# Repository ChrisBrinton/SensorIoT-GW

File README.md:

# SensorIoT

Consolidated repository for the SensorIoT environmental sensing system — all embedded firmware and hardware designs.

## Architecture

```
Sensor Nodes (ATmega328P + BME280 + RF95/RFM69)
        │
        │  915 MHz packet radio
        ▼
Gateway (ESP8266 + RF radio + WiFi + OLED)
        │
        │  WiFi / MQTT
        ▼
Backend Server (see SensorIoT-Broker repo)
```

## Components

### firmware/gateway/
ESP8266-based gateway that receives sensor data from nodes via RF radio and publishes to MQTT.
- RFM69 / RF95 (LoRa) radio receiver
- MQTT publisher over WiFi
- 128x32 OLED display for real-time readings
- Embedded web interface for configuration
- OTA firmware updates
- Built with PlatformIO

### firmware/node/
Battery-operated sensor nodes (ATmega328P) that measure temperature, humidity, and pressure.
- BME280 environmental sensor
- RFM69 / RF95 radio transmitter
- Low-power sleep modes for extended battery life
- Multiple firmware variants (RadioHead, RFM69, power-boost)
- Built with PlatformIO

### firmware/display/
ESP32-based standalone display module (work in progress).
- ESP32-WROVER-IE with WiFi/BLE
- LTR-329 ambient light sensor

### PCBs/
EAGLE CAD hardware designs for all boards:
- `gateway/` — Gateway board revisions (v1.13–1.16)
- `node/` — Sensor node board revisions (v1.3b–1.5)
- `display/` — Display module board
- `accessories/` — BME280 daughter boards, ISP programmers

## Sensors

| Measurement | Sensor | Units |
|-------------|--------|-------|
| Temperature | BME280 | °F |
| Humidity | BME280 | % RH |
| Pressure | BME280 | inHg |
| Battery | ADC | V |
| Signal | RSSI | dBm |

## Building

Each firmware component has its own PlatformIO project:

```bash
cd firmware/gateway
pio run                    # Build
pio run -t upload          # Flash via USB
pio run -e ota -t upload   # Flash via OTA
```

## Related Repositories

- **SensorIoT-Broker** — Backend services (MQTT broker, REST API, MongoDB)
- **SensorIoT_app** — React Native mobile app

## Consolidation History

This repo now contains code previously split across:
- `SensorIoT-GW` — Gateway firmware and PCBs (original home of this repo)
- `SensorIoT-Node` — Sensor node firmware and PCBs
- `SensorIoT-Display` — Display module hardware and firmware

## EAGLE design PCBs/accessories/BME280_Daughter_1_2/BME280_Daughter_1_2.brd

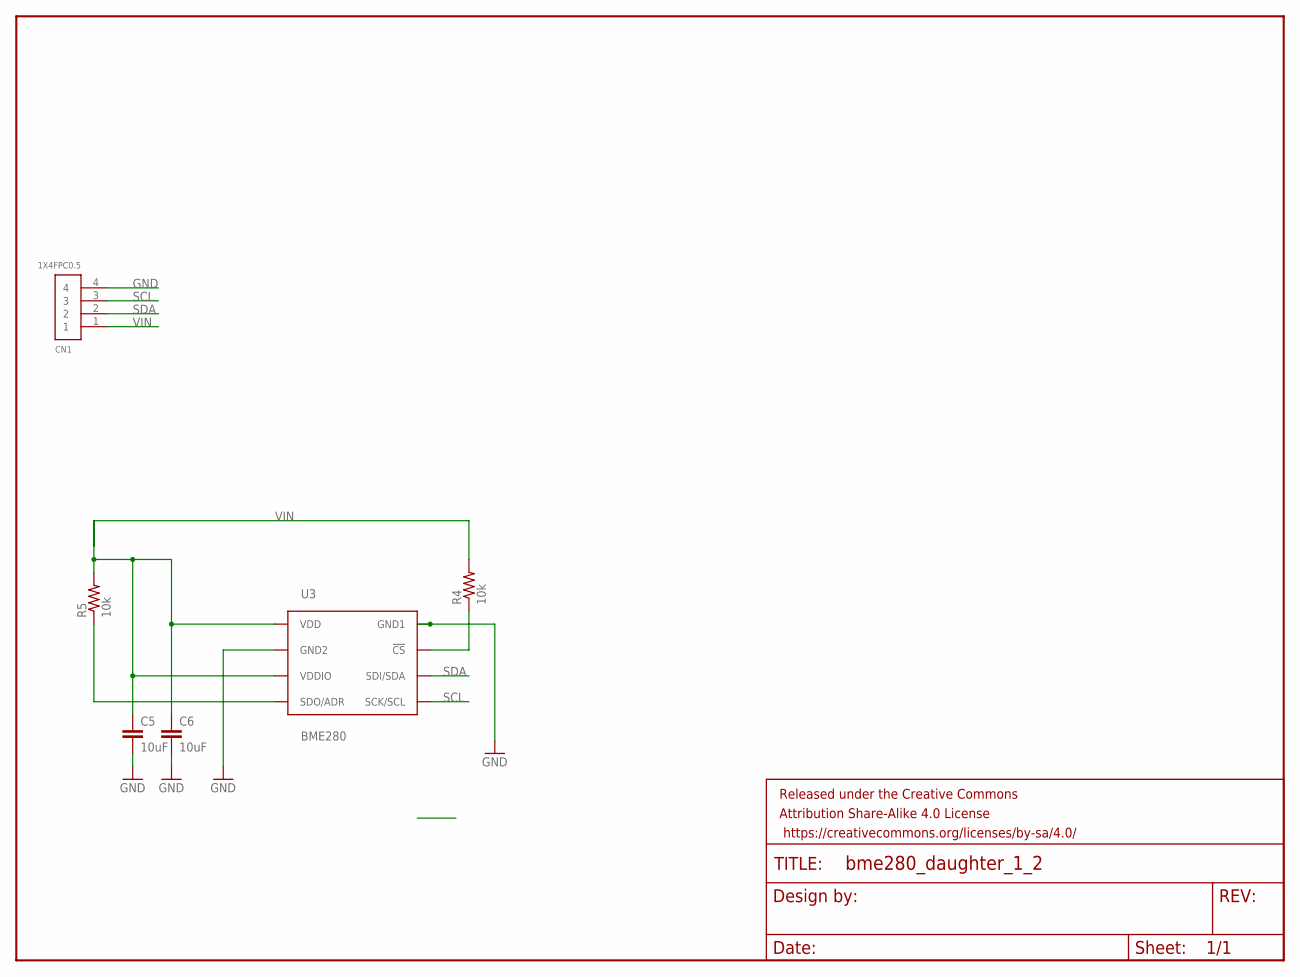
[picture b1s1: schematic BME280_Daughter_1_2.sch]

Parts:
C5, C6: 10uF; 0805
CN1: 1X4FPC0.5; FPC_0.5MM-4
FRAME1: FRAME-LETTER; CREATIVE_COMMONS
R4, R5: 10k; 0805
U3: BME280; BME280_LGA

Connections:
GND: C5.2, C6.2, CN1.4, U3.P$1 (GND1), U3.P$7 (GND2)
unnamed: R4.1, U3.P$2 (!CS)
unnamed: R5.1, U3.P$5 (SDO/ADR)
SCL: CN1.3, U3.P$4 (SCK/SCL)
SDA: CN1.2, U3.P$3 (SDI/SDA)
VIN: C5.1, C6.1, CN1.1, R4.2, R5.2, U3.P$6 (VDDIO), U3.P$8 (VDD)

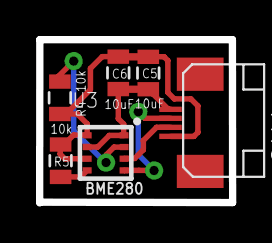
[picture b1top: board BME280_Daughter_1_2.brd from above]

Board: 2 copper layers, 10.7 x 9.1 mm, 7 parts (0 on the bottom side), 6 nets.

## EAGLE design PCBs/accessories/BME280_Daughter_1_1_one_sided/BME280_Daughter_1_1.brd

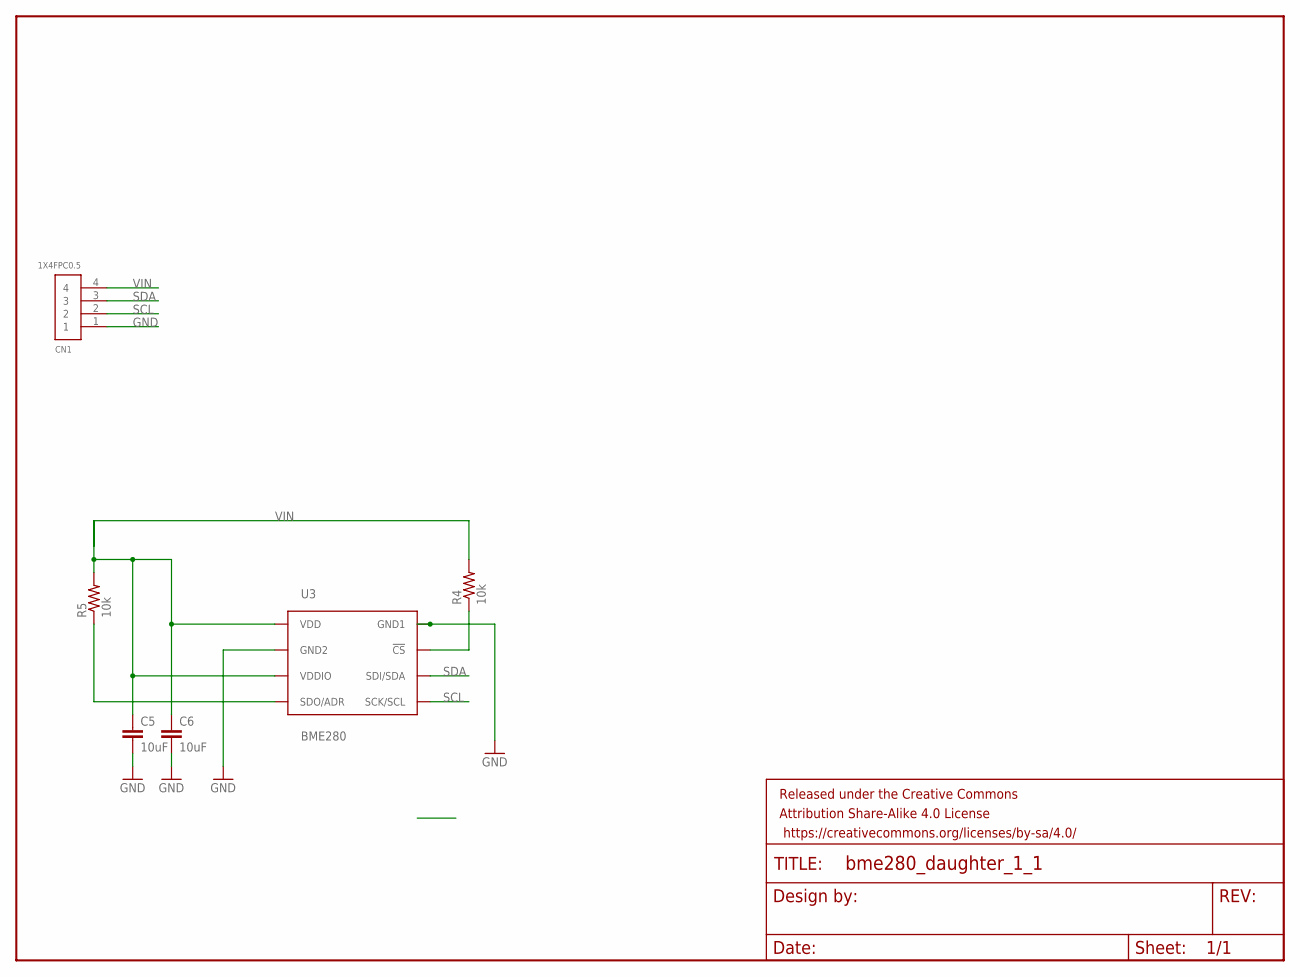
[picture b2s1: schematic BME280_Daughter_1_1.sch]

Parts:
C5, C6: 10uF; 0805
CN1: 1X4FPC0.5; FPC_0.5MM-4
FRAME1: FRAME-LETTER; CREATIVE_COMMONS
R4, R5: 10k; 0805
U3: BME280; BME280_LGA

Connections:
GND: C5.2, C6.2, CN1.1, U3.P$1 (GND1), U3.P$7 (GND2)
unnamed: R4.1, U3.P$2 (!CS)
unnamed: R5.1, U3.P$5 (SDO/ADR)
SCL: CN1.2, U3.P$4 (SCK/SCL)
SDA: CN1.3, U3.P$3 (SDI/SDA)
VIN: C5.1, C6.1, CN1.4, R4.2, R5.2, U3.P$6 (VDDIO), U3.P$8 (VDD)

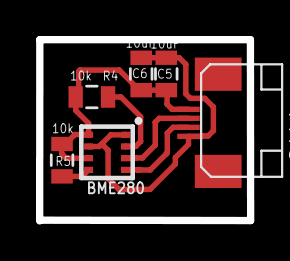
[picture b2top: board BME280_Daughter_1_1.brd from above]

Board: 2 copper layers, 11.7 x 10.1 mm, 7 parts (0 on the bottom side), 6 nets.

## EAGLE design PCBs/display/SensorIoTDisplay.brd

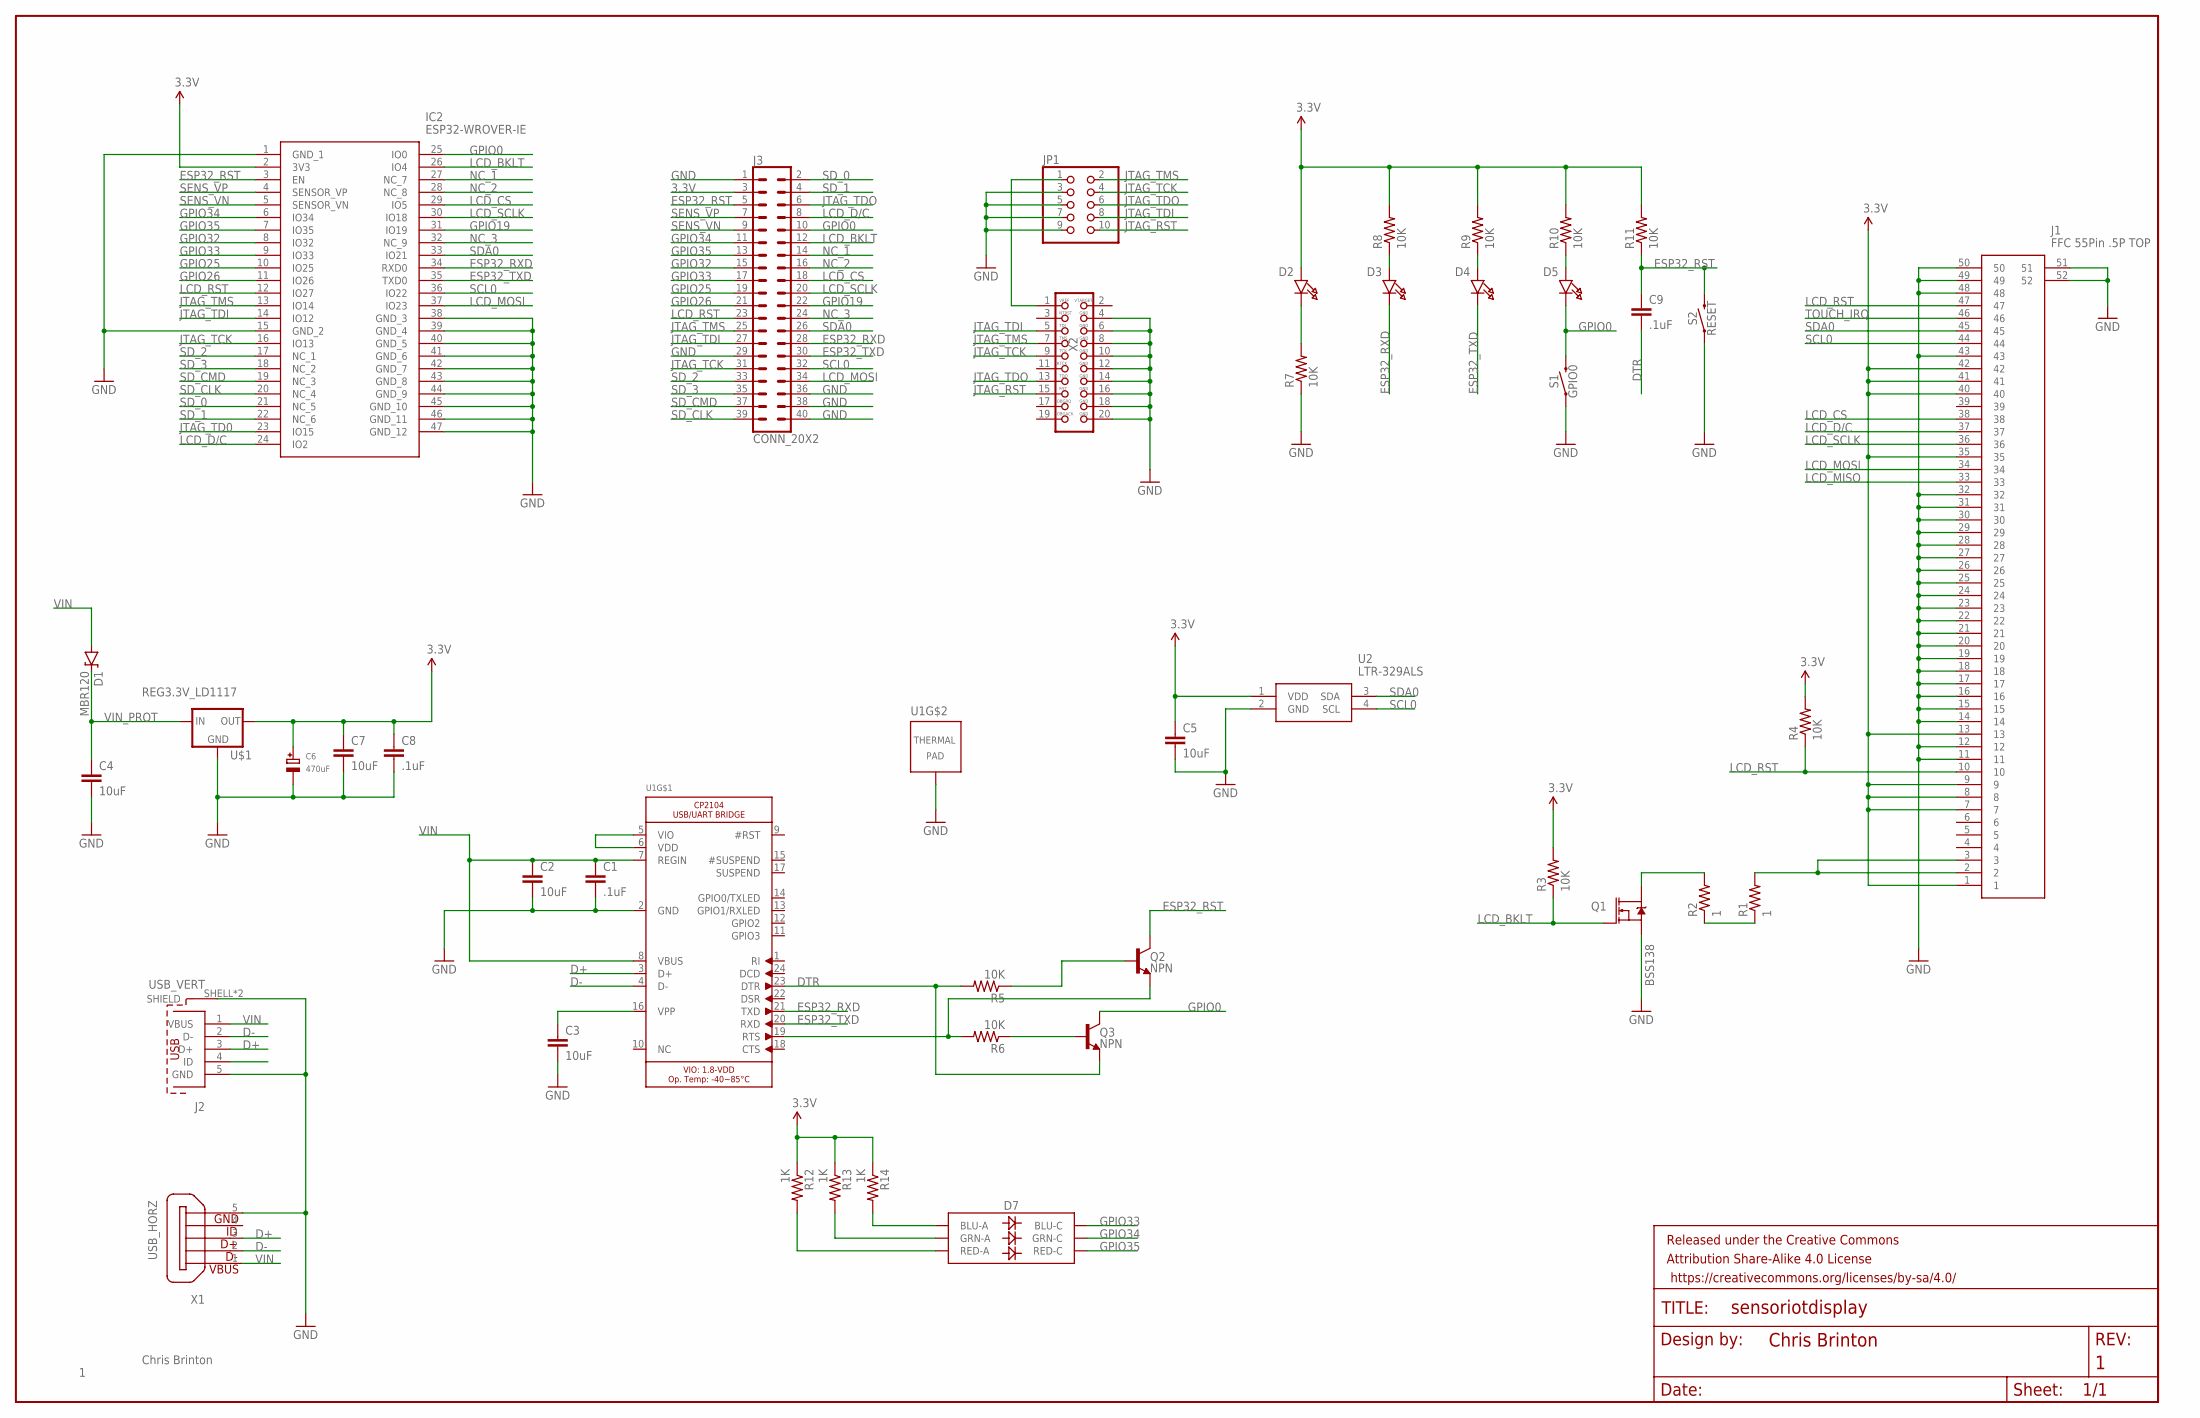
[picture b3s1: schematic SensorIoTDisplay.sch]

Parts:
C1, C8, C9: .1uF; 0805
C2, C3, C4, C5, C7: 10uF; 0805
C6: 470uF; EIA7343-31/D-R
D1: MBR120; SOD-123
D2: RED; CHIPLED_0805_NOOUTLINE
D3: GREEN; CHIPLED_0805_NOOUTLINE
D4, D5: BLUE; CHIPLED_0805_NOOUTLINE
D7: LED-RGBNO_IC; LED-TRICOLOR-5050
FRAME1: FRAME-LEDGER; CREATIVE_COMMONS
IC2: ESP32-WROVER-IE; ESP32WROVERIEM213EH6464UH3Q0
J1: FFC 55Pin .5P TOP; FH12A50S05SH55
J2: USB_VERT; 614105150621
J3: CONN_20X2; 2X20
JP1: HEADER-2X51.27MM; 2X05_1.27MM_SMT
Q1: BSS138; SOT23-3
Q2, Q3: NPN; SOT23-3
R1, R2: 1; 0805
R3, R4, R5, R6, R7, R8, R9, R10, R11: 10K; 0805
R12, R13, R14: 1K; 0805
S1: GPIO0; TACTILE_SWITCH_SMD_4.6X2.8MM
S2: RESET; TACTILE_SWITCH_SMD_4.6X2.8MM
U1: CP2104; QFN24_4MM_SMSC
U2: LTR-329ALS; LTR329ALS01
U$1: REG3.3V_LD1117; SOT223
X1: USB_HORZ; ZX62D-B-5PA8
X2: MICROBUILDER_JTAG-ARM7SMT_FEMALE; MICROBUILDER_2X10_SMT_FEMALE

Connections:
3.3V: C5.1, C6.+, C7.1, C8.1, D2.A, IC2.2 (3V3), J1.1, J1.7, J1.8, J1.9, J1.13, J1.35, J1.40, J1.41, J1.42, J3.3, R3.2, R4.2, R8.2, R9.2, R10.2, R11.2, R12.1, R13.1, R14.1, U2.1 (VDD), U$1.2 (OUT)
D+: J2.3 (D+), U1.3 (D+), X1.3
D-: J2.2 (D-), U1.4 (D-), X1.2
DTR: C9.2, Q3.2 (E), R5.2, U1.23 (DTR)
ESP32_RST: C9.1, IC2.3 (EN), J3.5, Q2.3 (C), R11.1, S2.3 (2), S2.4 (2)
ESP32_RXD: D3.C, IC2.34 (RXD0), J3.28, U1.21 (TXD)
ESP32_TXD: D4.C, IC2.35 (TXD0), J3.30, U1.20 (RXD)
GND: C1.2, C2.2, C3.2, C4.2, C5.2, C6.-, C7.2, C8.2, IC2.1 (GND_1), IC2.15 (GND_2), IC2.38 (GND_3), IC2.39 (GND_4), IC2.40 (GND_5), IC2.41 (GND_6), IC2.42 (GND_7), IC2.43 (GND_8), IC2.44 (GND_9), IC2.45 (GND_10), IC2.46 (GND_11), IC2.47 (GND_12), J1.11, J1.12, J1.14, J1.15, J1.16, J1.17, J1.18, J1.19, J1.20, J1.21, J1.22, J1.23, J1.24, J1.25, J1.26, J1.27, J1.28, J1.29, J1.30, J1.31, J1.32, J1.43, J1.48, J1.49, J1.50, J1.51, J1.52, J2.5 (GND), J2.SHELL (SHIELD), J2.SHELL1 (SHIELD), J3.1, J3.29, J3.36, J3.38, J3.40, JP1.3, JP1.5, JP1.7, JP1.9, Q1.2 (S), R7.1, S1.1, S1.2 (1), S2.1, S2.2 (1), U1.2 (GND), U1.THERM (TP), U2.2 (GND), U$1.1 (GND), X1.5, X2.4, X2.6, X2.8, X2.10, X2.12, X2.14, X2.16, X2.18, X2.20
GPIO0: D5.C, IC2.25 (IO0), J3.10, Q3.3 (C), S1.3 (2), S1.4 (2)
GPIO19: IC2.31 (IO19), J3.22
GPIO25: IC2.10 (IO25), J3.19
GPIO26: IC2.11 (IO26), J3.21
GPIO32: IC2.8 (IO32), J3.15
GPIO33: D7.4 (BLU-C), IC2.9 (IO33), J3.17
GPIO34: D7.6 (GRN-C), IC2.6 (IO34), J3.11
GPIO35: D7.5 (RED-C), IC2.7 (IO35), J3.13
JTAG_RST: JP1.10, X2.15
JTAG_TCK: IC2.16 (IO13), J3.31, JP1.4, X2.9
JTAG_TD0: IC2.23 (IO15)
JTAG_TDI: IC2.14 (IO12), J3.27, JP1.8, X2.5
JTAG_TDO: J3.6, JP1.6, X2.13
JTAG_TMS: IC2.13 (IO14), J3.25, JP1.2, X2.7
LCD_BKLT: IC2.26 (IO4), J3.12, Q1.1 (G), R3.1
LCD_CS: IC2.29 (IO5), J1.38, J3.18
LCD_D/C: IC2.24 (IO2), J1.37, J3.8
LCD_MISO: J1.33
LCD_MOSI: IC2.37 (IO23), J1.34, J3.34
LCD_RST: IC2.12 (IO27), J1.10, J1.47, J3.23, R4.1
LCD_SCLK: IC2.30 (IO18), J1.36, J3.20
unnamed: R1.1, R2.1
unnamed: J1.2, J1.3, R1.2
unnamed: Q1.3 (D), R2.2
unnamed: U1.5 (VIO), U1.6 (VDD)
unnamed: C3.1, U1.16 (VPP)
unnamed: D7.1 (GRN-A), R13.2
unnamed: Q2.2 (E), R6.2, U1.19 (RTS)
unnamed: Q3.1 (B), R6.1
unnamed: Q2.1 (B), R5.1
unnamed: D2.C, R7.2
unnamed: D7.2 (RED-A), R12.2
unnamed: D7.3 (BLU-A), R14.2
unnamed: D3.A, R8.1
unnamed: D4.A, R9.1
unnamed: D5.A, R10.1
unnamed: JP1.1, X2.1
NC_1: IC2.27 (NC_7), J3.14
NC_2: IC2.28 (NC_8), J3.16
NC_3: IC2.32 (NC_9), J3.24
SCL0: IC2.36 (IO22), J1.44, J3.32, U2.4 (SCL)
SDA0: IC2.33 (IO21), J1.45, J3.26, U2.3 (SDA)
SD_0: IC2.21 (NC_5), J3.2
SD_1: IC2.22 (NC_6), J3.4
SD_2: IC2.17 (NC_1), J3.33
SD_3: IC2.18 (NC_2), J3.35
SD_CLK: IC2.20 (NC_4), J3.39
SD_CMD: IC2.19 (NC_3), J3.37
SENS_VN: IC2.5 (SENSOR_VN), J3.9
SENS_VP: IC2.4 (SENSOR_VP), J3.7
TOUCH_IRQ: J1.46
VIN: C1.1, C2.1, D1.A, J2.1 (VBUS), U1.7 (REGIN), U1.8 (VBUS), X1.1
VIN_PROT: C4.1, D1.C, U$1.3 (IN)

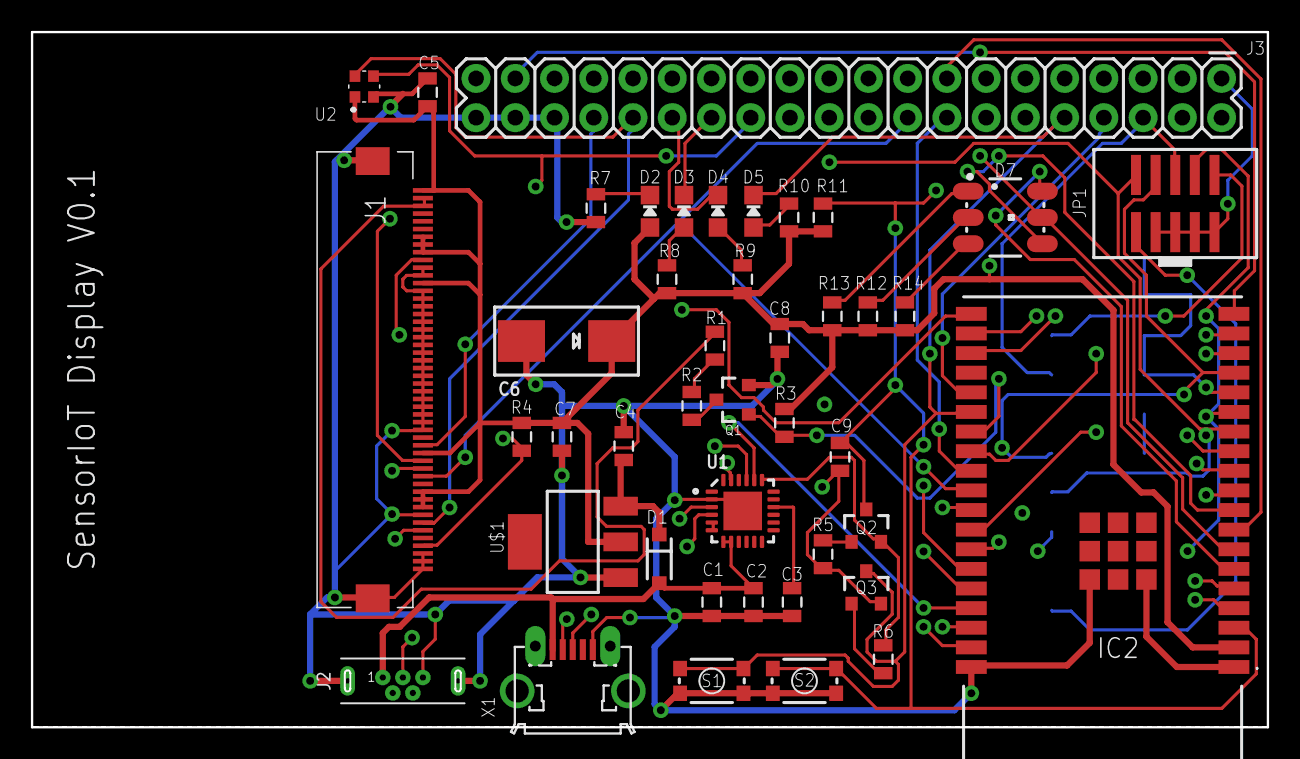
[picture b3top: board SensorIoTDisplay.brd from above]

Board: 4 copper layers, 80.0 x 45.0 mm, 45 parts (1 on the bottom side), 58 nets.

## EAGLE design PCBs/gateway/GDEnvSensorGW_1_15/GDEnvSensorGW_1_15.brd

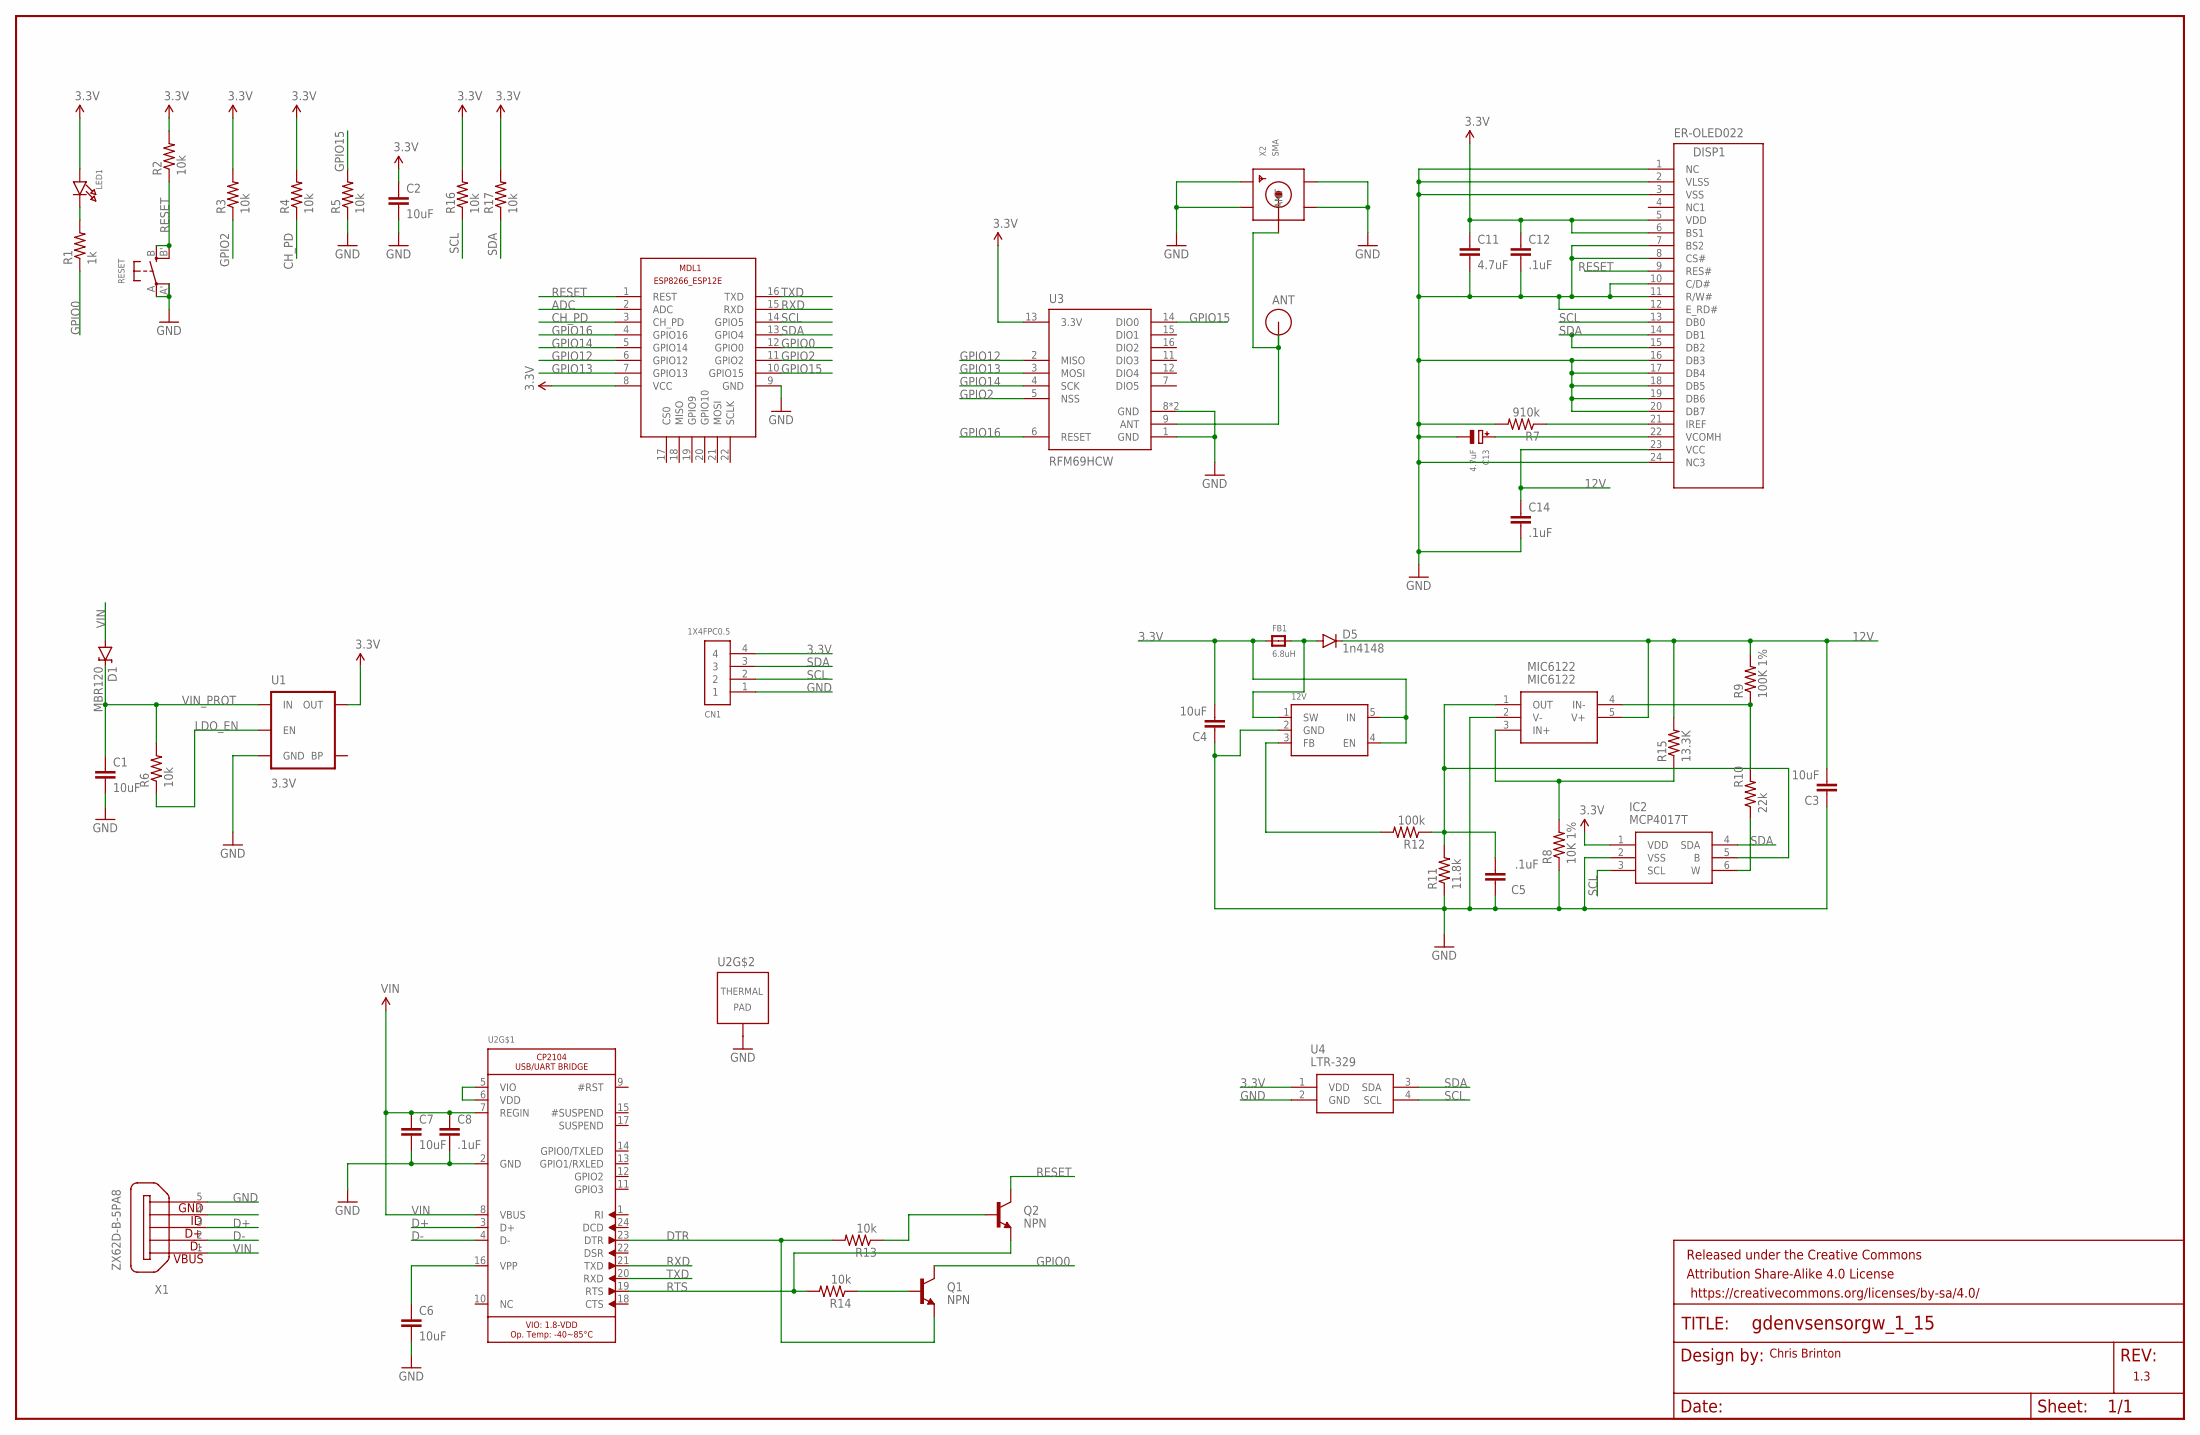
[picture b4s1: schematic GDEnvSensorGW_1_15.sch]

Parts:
12V: MP1541_SOT23-5; SOT23-5
ANT: RFM12B_ANTENNA; RFM12B-ANTENNA
C1, C2, C3, C4, C6, C7: 10uF; 0805-CAP
C5, C8, C12, C14: .1uF; 0805-CAP
C11: 4.7uF; 0805-CAP
C13: 4.7uF; EIA3216-18/A-R
CN1: 1X4FPC0.5; FPC_0.5MM-4
D1: MBR120; SOD-123
D5: 1n4148; SOD-323
DISP1: ER-OLED022
FB1: 6.8uH; _0805
FRAME1: FRAME-LEDGER; CREATIVE_COMMONS
IC2: MCP4017T; SOT65P210X110-6N
LED1: LED0805; CHIPLED_0805
MDL1: ESP8266-ESP12F; ESP8266-ESP12E
MIC6122: MIC6122; SOT95P280X145-5N
Q1, Q2: NPN; SOT23-3
R1: 1k; R0805
R2, R3, R4, R5, R6, R13, R14, R16, R17: 10k; R0805
R7: 910k; R0805
R8: 10K 1%; R0805
R9: 100K 1%; R0805
R10: 22k; R0805
R11: 11.8k; R0805
R12: 100k; R0805
R15: 13.3K; R0805
RESET: SWITCH_TACT_SMT4.6X2.8; BTN_KMR2_4.6X2.8
U1: 3.3V; SOT23-5
U2: CP2104; QFN24_4MM_SMSC
U3: RFM69HCW; RFM69HCW-XXXS2
U4: LTR-329; LTR329ALS01
X1: ZX62D-B-5PA8
X2: SMA; SMA_EDGELAUNCH_UFL

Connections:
3.3V: 12V.4 (EN), 12V.5 (IN), C2.1, C4.2, C11.1, C12.1, CN1.4, DISP1.5 (VDD), DISP1.6 (BS1), FB1.1, IC2.1 (VDD), LED1.A, MDL1.8 (VCC), R2.2, R3.2, R4.2, R16.2, R17.2, U1.5 (OUT), U3.13 (3.3V), U4.1 (VDD)
12V: C3.2, C14.1, D5.C, DISP1.23 (VCC), MIC6122.5 (V+), R9.2, R15.2
ADC: MDL1.2 (ADC)
ANT: ANT.P$1, U3.9 (ANT), X2.P (ANT)
CH_PD: MDL1.3 (CH_PD), R4.1
D+: U2.3 (D+), X1.3
D-: U2.4 (D-), X1.2
DTR: Q1.2 (E), R13.2, U2.23 (DTR)
GND: 12V.2 (GND), C1.2, C2.2, C3.1, C4.1, C5.1, C6.2, C7.2, C8.2, C11.2, C12.2, C13.-, C14.2, CN1.1, DISP1.1 (NC), DISP1.2 (VLSS), DISP1.3 (VSS), DISP1.7 (BS2), DISP1.8 (CS#), DISP1.10 (C/D#), DISP1.11 (R/W#), DISP1.12 (E_RD#), DISP1.16 (DB3), DISP1.17 (DB4), DISP1.18 (DB5), DISP1.19 (DB6), DISP1.20 (DB7), DISP1.24 (NC3), IC2.2 (VSS), MDL1.9 (GND), MIC6122.2 (V-), R5.1, R7.2, R8.1, R11.1, RESET.A, RESET.A' (P1), U1.2 (GND), U2.2 (GND), U2.THERM (TP), U3.1 (GND), U3.8 (GND), U3.10 (GND), U4.2 (GND), X1.5, X2.GND@1 (GND1), X2.GND@2 (GND2), X2.GND@3 (GND3), X2.GND@4 (GND4)
GPIO0: MDL1.12 (GPIO0), Q1.3 (C), R1.1
GPIO2: MDL1.11 (GPIO2), R3.1, U3.5 (NSS)
GPIO12: MDL1.6 (GPIO12), U3.2 (MISO)
GPIO13: MDL1.7 (GPIO13), U3.3 (MOSI)
GPIO14: MDL1.5 (GPIO14), U3.4 (SCK)
GPIO15: MDL1.10 (GPIO15), R5.2, U3.14 (DIO0)
GPIO16: MDL1.4 (GPIO16), U3.6 (RESET)
LDO_EN: R6.1, U1.3 (EN)
unnamed: U2.5 (VIO), U2.6 (VDD)
unnamed: MIC6122.3 (IN+), R8.2, R15.1
unnamed: LED1.C, R1.2
unnamed: C13.+, DISP1.22 (VCOMH)
unnamed: C6.1, U2.16 (VPP)
unnamed: C5.2, IC2.5 (B), MIC6122.1 (OUT), R11.2, R12.1
unnamed: MIC6122.4 (IN-), R9.1, R10.2
unnamed: 12V.1 (SW), D5.A, FB1.2
unnamed: Q2.1 (B), R13.1
unnamed: DISP1.21 (IREF), R7.1
unnamed: IC2.6 (W), R10.1
unnamed: 12V.3 (FB), R12.2
unnamed: Q1.1 (B), R14.1
RESET: DISP1.9 (RES#), MDL1.1 (REST), Q2.3 (C), R2.1, RESET.B (S), RESET.B' (S1)
RTS: Q2.2 (E), R14.2, U2.19 (RTS)
RXD: MDL1.15 (RXD), U2.21 (TXD)
SCL: CN1.2, DISP1.13 (DB0), IC2.3 (SCL), MDL1.14 (GPIO5), R16.1, U4.4 (SCL)
SDA: CN1.3, DISP1.14 (DB1), DISP1.15 (DB2), IC2.4 (SDA), MDL1.13 (GPIO4), R17.1, U4.3 (SDA)
TXD: MDL1.16 (TXD), U2.20 (RXD)
VIN: C7.1, C8.1, D1.A, U2.7 (REGIN), U2.8 (VBUS), X1.1
VIN_PROT: C1.1, D1.C, R6.2, U1.1 (IN)

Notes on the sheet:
Chris Brinton
1.3

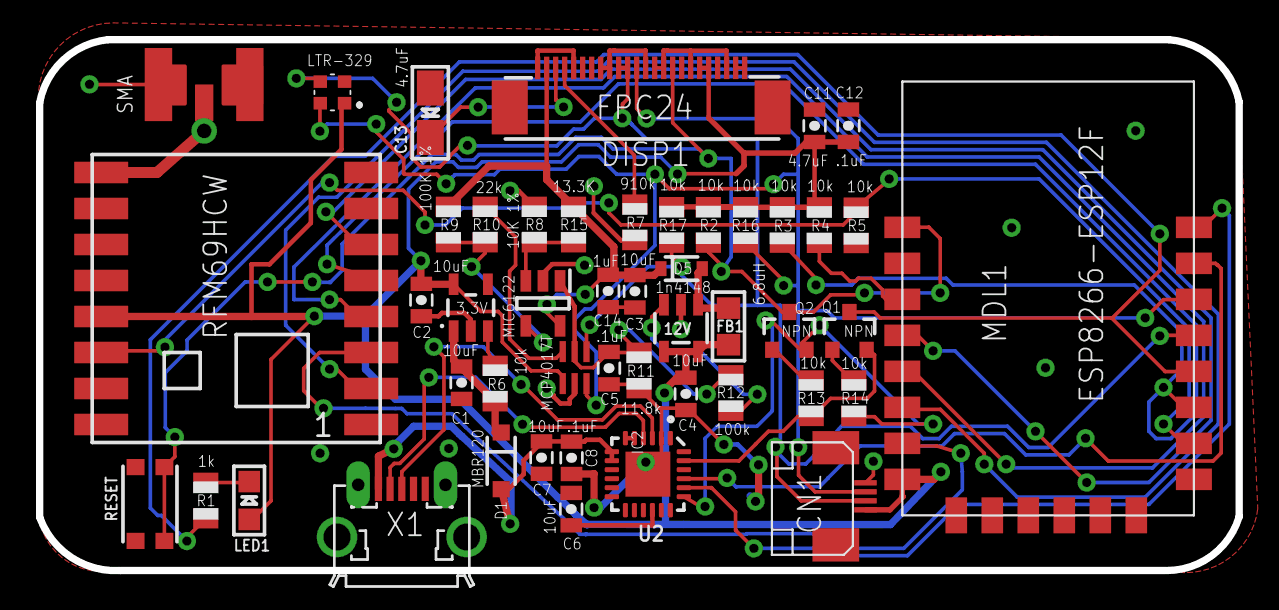
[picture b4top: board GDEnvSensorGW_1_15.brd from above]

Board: 2 copper layers, 66.6 x 29.5 mm, 50 parts (0 on the bottom side), 37 nets.

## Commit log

2018-10-31 Initial commit under VSCode to new GW repo, SensorIoT-GW. Based on firmware ver 1.0.4
2018-11-05 Changed AP Mode display info, also increase wifi reconnect timer to 10min. Should allow easier editing of network info during initial config
2018-12-20 v1.0.5 - bug fix for time display jitter, change topic matching to use strings, reorganize folders
2019-01-02 1.0.6 - Add firmware uploader to web.ino and html
2019-01-10 Full support of http FW upload capability. Non-blocking display code.
2019-02-15 Updated instructions
2019-02-16 Update instructions
2019-02-16 Fix lint issues
2019-02-18 Bring libraries up to date, improve README.md
2019-02-18 improve README
2019-02-27 retrieve nicknames via mqtt, update readme
2019-03-28 Add 1305 single buffer support
2019-03-28 Reverse FPC connector wiring to support new cables
2019-03-28 build for v1.0.7
2019-03-28 Specify platformio core 1.6.0
2019-03-28 add data/
2019-03-28 Add display defines, remove NTP client debug
2019-03-28 v1.0.9 features: display redesign and web config.
2019-03-28 fix to clientID and checkbox setting update
2019-03-28 v1.0.9 details
2019-05-02 add builds to repo
2019-06-18 Version 1.15 of GW board
2019-06-19 1.0.9 rc4
2019-10-18 Refactor for RFM95 support
2019-10-18 New vertical USB connector
2019-10-18 Changes for RFM95 & LTR 329
2019-10-18 Bump lodash from 4.17.11 to 4.17.13 in /firmware
    Bumps [lodash](https://github.com/lodash/lodash) from 4.17.11 to 4.17.13.
    - [Release notes](https://github.com/lodash/lodash/releases)
    - [Commits](https://github.com/lodash/lodash/compare/4.17.11...4.17.13)
2019-10-18 Bump lodash.merge from 4.6.1 to 4.6.2 in /firmware
    Bumps [lodash.merge](https://github.com/lodash/lodash) from 4.6.1 to 4.6.2.
    - [Release notes](https://github.com/lodash/lodash/releases)
    - [Commits](https://github.com/lodash/lodash/commits)
2019-10-18 Bump mixin-deep from 1.3.1 to 1.3.2 in /firmware
    Bumps [mixin-deep](https://github.com/jonschlinkert/mixin-deep) from 1.3.1 to 1.3.2.
    - [Release notes](https://github.com/jonschlinkert/mixin-deep/releases)
    - [Commits](https://github.com/jonschlinkert/mixin-deep/compare/1.3.1...1.3.2)
2019-10-22 New platformio dir struct
2019-10-22 v1.0.10
2019-10-22 v1.1.2
2019-10-22 build v1.0.10
2019-10-22 NodeList fix for deleteNode() crash
2019-10-22 add 1.0.10 build
2019-11-04 Fix keepalive and ntp DST
2019-11-04 rebuild with new ntp client lib
2019-11-10 cleanup, fix compile warnings
2019-11-11 lib updates
2019-11-11 v1.1.4
2019-11-11 new ver
2019-11-13 platformio core to 2.2.3 and lib updates to match.
2019-11-13 add build
2019-11-19 Report heap spc "Beat" even if not conn to MQTT
2019-11-19 Only reset wifi if wifi config changes
2019-11-19 Disable local DNS due to memory leak
2019-11-19 lock in radio head 1.97
2019-11-19 dont specify comm port
2019-11-19 rebuild
2019-11-19 cleanup builds
2020-07-16 Bump lodash from 4.17.13 to 4.17.19 in /firmware
    Bumps [lodash](https://github.com/lodash/lodash) from 4.17.13 to 4.17.19.
    - [Release notes](https://github.com/lodash/lodash/releases)
    - [Commits](https://github.com/lodash/lodash/compare/4.17.13...4.17.19)
2020-12-11 Bump ini from 1.3.5 to 1.3.7 in /firmware
    Bumps [ini](https://github.com/isaacs/ini) from 1.3.5 to 1.3.7.
    - [Release notes](https://github.com/isaacs/ini/releases)
    - [Commits](https://github.com/isaacs/ini/compare/v1.3.5...v1.3.7)
2021-03-31 Ver 1.1.6
2021-03-31 update ntp lib and add correct config
2021-05-08 Bump lodash from 4.17.13 to 4.17.21 in /firmware
    Bumps [lodash](https://github.com/lodash/lodash) from 4.17.13 to 4.17.21.
    - [Release notes](https://github.com/lodash/lodash/releases)
    - [Commits](https://github.com/lodash/lodash/compare/4.17.13...4.17.21)
2021-08-10 Bump path-parse from 1.0.6 to 1.0.7 in /firmware
    Bumps [path-parse](https://github.com/jbgutierrez/path-parse) from 1.0.6 to 1.0.7.
    - [Release notes](https://github.com/jbgutierrez/path-parse/releases)
    - [Commits](https://github.com/jbgutierrez/path-parse/commits/v1.0.7)
    ---
    updated-dependencies:
    - dependency-name: path-parse
2022-11-03 Bump minimatch and gulp in /firmware
    Bumps [minimatch](https://github.com/isaacs/minimatch) to 3.0.4 and updates ancestor dependency [gulp](https://github.com/gulpjs/gulp). These dependencies need to be updated together.
    Updates `minimatch` from 0.2.14 to 3.0.4
    - [Release notes](https://github.com/isaacs/minimatch/releases)
    - [Commits](https://github.com/isaacs/minimatch/compare/v0.2.14...v3.0.4)
    Updates `gulp` from 3.9.1 to 4.0.2
    - [Release notes](https://github.com/gulpjs/gulp/releases)
2022-12-03 Bump decode-uri-component from 0.2.0 to 0.2.2 in /firmware
    Bumps [decode-uri-component](https://github.com/SamVerschueren/decode-uri-component) from 0.2.0 to 0.2.2.
    - [Release notes](https://github.com/SamVerschueren/decode-uri-component/releases)
    - [Commits](https://github.com/SamVerschueren/decode-uri-component/compare/v0.2.0...v0.2.2)
    ---
    updated-dependencies:
    - dependency-name: decode-uri-component
2023-08-08 in progress clock work
2025-04-03 more readme
2026-03-19 Consolidate embedded firmware and hardware into unified repo
    Restructure to absorb SensorIoT-Node and SensorIoT-Display:
    - firmware/gateway/ - ESP8266 gateway (moved from firmware root)
    - firmware/node/ - ATmega328P sensor nodes (from SensorIoT-Node)
    - firmware/display/ - ESP32 display module (from SensorIoT-Display)
    - PCBs/gateway/ - Gateway board designs (reorganized)
    - PCBs/node/ - Sensor node board designs (from SensorIoT-Node)

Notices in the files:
parts and their libraries:
SparkFun-Capacitors: Licensing: Creative Commons ShareAlike 4.0 International - https://creativecommons.org/licenses/by-sa/4.0
SparkFun-Aesthetics: Released under the Creative Commons Attribution Share-Alike 4.0 License
SparkFun-Aesthetics: https://creativecommons.org/licenses/by-sa/4.0
